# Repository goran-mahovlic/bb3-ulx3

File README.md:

# Mix of BB3 ULX3S

Current version does not have SDRAM on FPGA

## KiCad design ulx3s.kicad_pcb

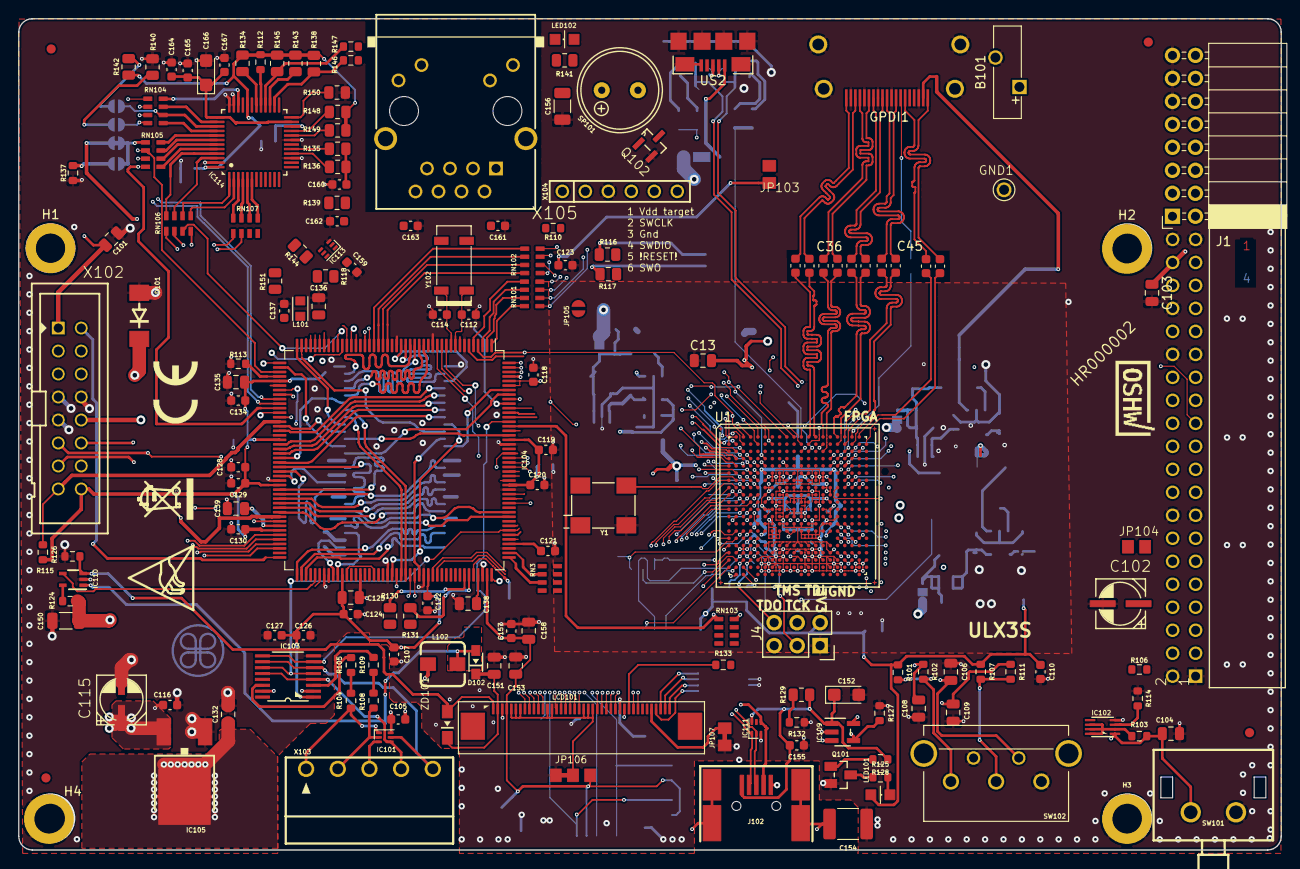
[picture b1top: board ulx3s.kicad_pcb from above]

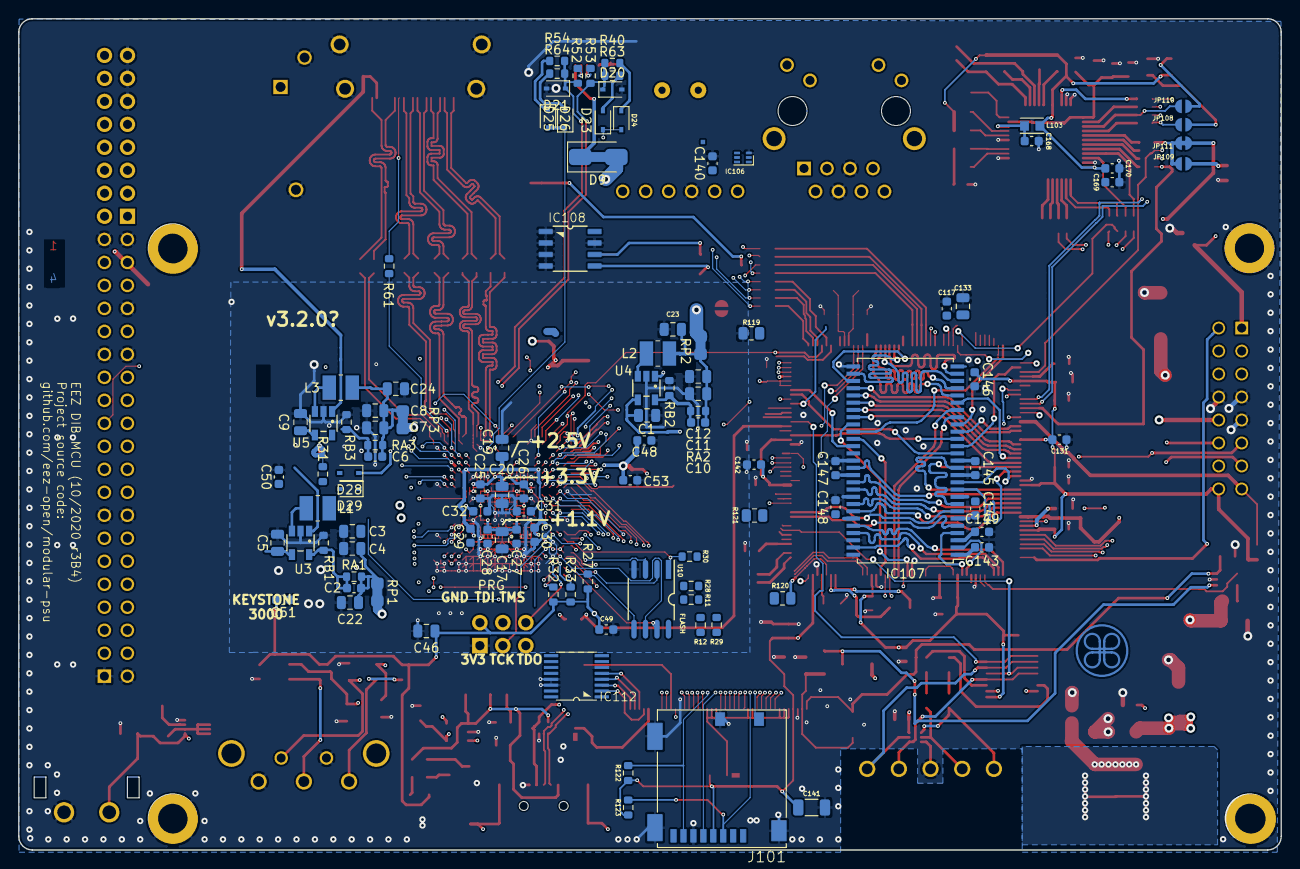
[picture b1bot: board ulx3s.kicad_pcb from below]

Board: 4 copper layers, 139.5 x 91.8 mm, 278 parts (104 on the bottom side), 327 nets.

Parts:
B101: DS1092-10-W6L; Battery_Panasonic_CR1025-VSK_Vertical_CircularHoles
C1, C3, C4, C5, C7, C8, C9, C11, C12: 22uF; C_0805_2012Metric
C2, C6, C10: 470pF; C_0603_1608Metric
C13, C17, C19, C20, C22, C23, C24, C46: 2.2uF; C_0805_2012Metric
C25, C26, C27, C28, C29, C30, C31, C32, C48, C49, C50, C51, C53: 22nF; C_0603_1608Metric
C36, C37, C38, C39, C40, C41, C42, C43, C44, C45: 220nF; C_0603_1608Metric
C101: N.C.; C_0805_2012Metric
C102, C115: EEEFK1V220R; PANASONIC_C
C103, C132, C133, C138, C139, C153: 2u2; C_0805_2012Metric
C104, C106, C108, C109: 10n; C_0805_2012Metric
C105, C107, C110, C116, C117, C118, C119, C120, C121, C122, C123, C124, C126, C127, C128, C129, C130, C131, C134, C137, C142, C143, C144, C145, C146, C147, C148, C149, C155, C157, C160, C161, C162, C163, C164, C165, C167, C168, C169, C170: 100n; C_0603_1608Metric
C112, C114: 4p7; C_0603_1608Metric
C125, C135, C136, C151, C158: 1u; C_0805_2012Metric
C140, C159: N.C.; C_0603_1608Metric
C141, C150, C156: 4u7; C_1206_3216Metric
C152: 4u7; CP_EIA-3216-10_Kemet-I
C154: 4n7/1kV; C_1812_4532Metric
C166: 10uF; CP_EIA-3216-10_Kemet-I
D9: 0; D_SMA_Jumper_NC
D20, D21: 3.6V; D_SOD-323
D23, D24, D25, D26, D28, D29: 1N914; D_SOD-323
D101: SMBJ5.0A-TR; DO214AA
D102: RB751V40T1G; SOD323-R
EEZ_SIGNATURE: SIGNATURESMALL; SIGNATURE_5MM
FM1, FM2, FM3, FM4: FIDUCIAL
GND1: PCB_TEST_TABSHIELD; PCB_SHIELD_TAB
GPDI1: GPDI-D; CONN-10029449-111RLF
H1, H2, H3, H4: HOLE; MountingHole_3.2mm_M3_ISO14580_Pad
IC101, IC111: TPD4E001DRLR; DRL6
IC102: 74AUP1G74DC.125; DCU8
IC103: CD74HC4050PWR; PW16
IC104: STM32F769IIT6; LQFP-176_24x24mm_P0.5mm
IC105: LD1117ADT33TR; DPACK
IC106, IC113: N.C.; DRL6
IC107: IS42S16400J; TSOP-II-54_22.2x10.16mm_P0.8mm
IC108: AT24C256C-SSHL-B; SOIC127P600X173-8N
IC109: TPS2051BDBVR; DBV5
IC110: TPS61169DCKR; DCK5
IC112: TSC2007IPW; PW(R-PDSO-G16)
IC114: DP83848CVV_NOPB; PT48
J1: Conn_02x08_Odd_Even; PinSocket_2x08_P2.54mm_Horizontal
J4: CONN_02X03; Socket_Strip_Straight_2x03
J101: 503398-1892; 5033981892
J102: 67803-8020; 678038020
JP103, JP104: JP2-CUT-0805; R_0805
JP105, JP108, JP109, JP110: JP2-CUT
JP106: JP3-CUT-0805-ROTATED; JP3-0805-CUT2
JP107: JP2-NOCUT-0805; JP2-0805-NOCUT
JP111: JP2-NOCUT
L1, L2, L3: 2.2uH; L_1008_1210
L101, L103: BLM18AG102SH1D; BEAD0603
L102: DLG-0403-4R7; DE0403
LABEL1: HR000002; CERT-SMALL-SILK
LCD101: 505110-4091; FPC_40
LED101, LED102: N.C.; LED_0805
Q101: N.C.; SOT23-BEC
Q102: 2N7002; SOT103P240X110-3N
R11, R12, R27, R28: 10k; R_0603_1608Metric
R29, R40, R54: 1.1k; R_0603_1608Metric
R30: 4.7k; R_0603_1608Metric
R31, R32, R33, R63, R64: 15k; R_0603_1608Metric
R52, R53: 27; R_0603_1608Metric
R61: 549; R_0603_1608Metric
R101, R104, R105, R107, R108, R109, R112, R115: 4K7; R_0603_1608Metric
R102, R103, R111, R113, R127, R132, R133: 10K; R_0603_1608Metric
R106, R110: 1K; R_0603_1608Metric
R114, R125, R128, R137: N.C.; R_0603_1608Metric
R116, R117, R134: 1K5; R_0805_2012Metric
R118: 47R; R_0805_2012Metric
R119, R120, R121, R140, R141, R142: N.C.; R_0805_2012Metric
R122, R123: 47K; R_0603_1608Metric
R124, R126: 10R; R_0603_1608Metric
R129: 4K7; R_0805_2012Metric
R130, R131: 22R; R_0805_2012Metric
R135, R136, R139, R144: 49R9; R_0805_2012Metric
R138, R143, R145, R148, R149, R151: 2K2; R_0805_2012Metric
R146, R147: 220R; R_0603_1608Metric
R150: 4K87; R_0805_2012Metric
RA1, RA2, RA3: 15k; R_0603_1608Metric
RB1: 18k; R_0603_1608Metric
RB2: 4.7k; R_0603_1608Metric
RB3: 3.3k; R_0603_1608Metric
RN3, RN101, RN102, RN103, RN104, RN105, RN106, RN107: DR1206-33R-4/8; CAY16
RP1, RP2, RP3: 0; R_0805_2012Metric_Pad1.29x1.40mm_HandSolder_Jumper_NC
SH101: SHORTNOHOLE; SHORT_NOHOLE
SP101: LD-BZEN 0903; LD-BZEN-0903
SW101: TL1100CF160Q; TL1100C
SW102: PEC16-2215F-S0024; PEC16-2215F
U1: LFE5U-85F-6BG381C; BGA-381_pitch0.8mm_dia0.4mm
U3, U4, U5: TLV62569DBV; TSOT-25
U10: IS25LP128F-JBLE; SOA008-150-208mil
U$1: RECYCLE_BIN1_8
U$2: CE_5MM
U$6: ESD_SYMBOL
US2: MICRO_USB; USB-MICRO-B-FCI-10118192-0001LF
X101: DS1024-2*20R0; ZL263-40DG
X102: DS1013-16SSIB1; IDC-16PIN
X103: 691322110005; MC1,5_5-G-3,5
X104: N.C.; SSW-106-02-S-S
X105: LMJTAB881243M-L; RJ45-TRAFO-LED
Y1: FNETHE025; Crystal_SMD_7050_4Pads
Y102: XTAL016178-85SMX; 85SMX
ZD101: BZX384-B24.115; SOD323-W

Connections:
+1V1: C17.1, C27.1, C28.1, J1.12, RP1.2, U1.H8, U1.H9, U1.H10, U1.H11, U1.H12, U1.H13, U1.J8, U1.J13, U1.K8, U1.K13, U1.L8, U1.L13, U1.M8, U1.M13, U1.N8, U1.N9, U1.N10, U1.N11, U1.N12, U1.N13, U1.T6, U1.T7, U1.T8, U1.T9, U1.T10, U1.T11, U1.T12, U1.T13, U1.T14, U1.T15, U1.U6, U1.U15
+2V5: C19.1, C29.1, C30.1, J1.14, RP2.2, U1.F6, U1.F15, U1.P6, U1.P15, U1.V10, U1.V11, U1.V17, U1.V18
+3V3: C13.2, C20.1, C25.1, C26.1, C31.1, C32.1, C46.1, C48.1, C49.1, C50.1, C51.1, C53.1, C102.1, C107.1, C110.1, C117.1, C118.1, C119.1, C120.1, C121.1, C122.1, C124.1, C125.1, C126.1, C127.1, C128.1, C129.1, C130.1, C131.1, C132.1, C133.1, C134.1, C135.1, C140.1, C141.1, C142.2, C143.1, C144.1, C145.1, C146.1, C147.1, C148.1, C149.1, C153.1, C156.2, C157.2, C158.2, C159.1, C169.1, C170.1, IC102.2, IC102.6, IC102.7, IC102.8, IC103.1, IC104.15, IC104.23, IC104.36, IC104.49, IC104.62, IC104.72, IC104.82, IC104.96, IC104.99, IC104.118, IC104.131, IC104.136, IC104.149, IC104.159, IC104.171, IC104.172, IC105.4, IC106.6, IC107.1, IC107.3, IC107.9, IC107.14, IC107.27, IC107.43, IC107.49, IC108.8, IC112.1, IC113.6, IC114.32, IC114.48, J1.16, J4.2, J101.4, JP105.1, JP106.NO, L101.P$1, L103.P$1, LCD101.4, LED101.A, R11.1, R12.1, R27.1, R28.1, R29.1, R30.1, R31.1, R32.1, R33.1, R101.1, R103.1, R107.1, R112.1, R115.1, R116.1, R117.1, R122.1, R123.1, R133.2, R134.2, R138.1, R141.1, R142.1, R143.1, R145.1, R148.1, R149.1, R151.1, RP3.2, SH101.P$2, U1.F9, U1.F10, U1.F11, U1.F12, U1.H6, U1.H7, U1.H14, U1.H15, U1.J6, U1.J15, U1.L6, U1.L7, U1.L14, U1.L15, U1.M6, U1.M15, U1.P9, U1.P10, U1.T2, U1.T3, U1.T4, U1.U2, U10.8, X101.7, X102.16, X105.9, X105.12, Y1.1, Y1.4
+3V3(A): C161.2, C163.2, C168.1, IC114.22, L103.P$2, X105.3, X105.6
+5V: C1.1, C5.1, C9.1, C105.1, C115.1, C116.1, C150.1, D9.2, D101.C, GPDI1.18, IC101.6, IC105.3, IC109.5, L102.1, R124.1, U3.1, U3.4, U4.1, U4.4, U5.1, U5.4, X101.35, X101.36, X102.5, X102.6
+12V: C103.1, X101.37, X101.38, X102.3, X102.4
+VAUX: JP103.2, X102.10
+VAUX_OUT: JP104.2, X101.5
/Envox SDRAM/TCK: IC106.1, R121.2, X104.2
/Envox SDRAM/TMS: IC106.2, R120.2, X104.4
/Envox_STM32/BYPASS_REG: IC104.48, R113.2
/Envox_STM32/RCC_OSC32_IN: C112.1, IC104.9, Y102.1
/Envox_STM32/RCC_OSC32_OUT: C114.1, IC104.10, Y102.4
/Envox_STM32/VBAT: B101.+, C123.1, IC104.6, JP103.1, JP104.1
/Envox_STM32/VCAP1: C139.1, IC104.81
/Envox_STM32/VCAP2: C138.1, IC104.129
/Envox_STM32/VDDA: C136.1, C137.1, IC104.39, L101.P$2, R118.2
/Envox_STM32/VREF+: IC104.38, R118.1
/Ethernet/LED_ACT: IC114.26, R138.2, R146.2
/Ethernet/LED_LINK: IC114.28, R145.2, R147.2
/Ethernet/LED_SPEED: IC114.27, LED102.C, R143.2
/TFT_LCD/LCD_DISP: LCD101.31, R133.1
/TFT_LCD/USB_D_N: IC111.1, J102.2, R130.1
/TFT_LCD/USB_D_P: IC111.2, J102.3, R131.1
/TFT_LCD/VLED+: C151.1, D102.C, LCD101.2, ZD101.C
/TFT_LCD/VLED-: IC110.3, LCD101.1, R126.1, ZD101.A
/TFT_LCD/XL: IC112.4, LCD101.39
/TFT_LCD/XR: IC112.2, LCD101.37
/TFT_LCD/YD: IC112.5, LCD101.38
/TFT_LCD/YU: IC112.3, LCD101.40
/flash/FLASH_MISO: R28.2, U1.V2, U10.2
/flash/FLASH_MOSI: R27.2, U1.W2, U10.5
/flash/FLASH_SCK: R29.2, U1.U3, U10.6
/flash/FLASH_nCS: R30.2, U1.R2, U10.1
/flash/FLASH_nHOLD: R12.2, U1.W1, U10.7
/flash/FLASH_nWP: R11.2, U1.Y2, U10.3
/flash/FPGA_DONE: R32.2, U1.Y3
/flash/FPGA_INITN: R33.2, U1.V3
/flash/FPGA_PROGRAMN: D28.2, D29.2, R31.2, U1.W3
/gpdi/FPDI_CEC: R61.2, U1.A18
/gpdi/GPDI_CLK+: C45.2, GPDI1.10
/gpdi/GPDI_CLK-: C41.2, GPDI1.12
/gpdi/GPDI_D0+: C44.2, GPDI1.7
/gpdi/GPDI_D0-: C40.2, GPDI1.9
/gpdi/GPDI_D1+: C43.2, GPDI1.4
/gpdi/GPDI_D1-: C39.2, GPDI1.6
/gpdi/GPDI_D2+: C42.2, GPDI1.1
/gpdi/GPDI_D2-: C38.2, GPDI1.3
/gpdi/GPDI_ETH+: C36.2, GPDI1.14
/gpdi/GPDI_ETH-: C37.2, GPDI1.19
/power/FB1: C2.2, RA1.2, RB1.2, U3.5
/power/FB2: C10.2, RA2.2, RB2.2, U4.5
/power/FB3: C6.2, RA3.2, RB3.2, U5.5
/power/L1: L1.1, U3.3
/power/L2: L2.1, U4.3
/power/L3: L3.1, U5.3
/power/P1V1: C2.1, C3.1, C4.1, C22.1, L1.2, RA1.1, RP1.1
/power/P2V5: C10.1, C11.1, C12.1, C23.1, L2.2, RA2.1, RP2.1
/power/P3V3: C6.1, C7.1, C8.1, C24.1, L3.2, RA3.1, RP3.1
/usb/FPD+: R53.2, US2.3
/usb/FPD-: R52.2, US2.2
/usb/US2VBUS: D9.1, US2.1
BOOT0: IC102.3, IC104.166, R114.2
CLK_25MHz: U1.G2, Y1.3
CLK_TO_ETH: RN104.1, U1.B11
CLK_TO_STM32: IC104.29, U1.A9
DAC_OUT1: IC104.50, Q102.1
DIN2: IC104.8, R110.2
DOUT2: IC103.7, IC103.9, IC104.163
ENC_A: C108.2, IC104.119, R102.1
ENC_B: C109.1, IC104.120, R111.1
ENC_SW: C106.2, IC104.173, SW102.E
ETH_COL: IC104.47, RN105.2
ETH_CRS: IC104.40, JP108.1, RN104.4
ETH_MDC: IC104.33, IC114.31
ETH_MDIO: IC104.42, IC114.30, R134.1
ETH_RXD0: IC104.54, RN105.3
ETH_RXD1: IC104.55, RN105.4
ETH_RXD2: IC104.83, RN106.1
ETH_RXD3: IC104.84, RN106.2
ETH_RX_CLK: IC104.41, RN104.2
ETH_RX_DV: IC104.53, RN104.3
ETH_RX_ERR: IC104.79, JP111.2
ETH_TXD0: IC104.85, RN107.1
ETH_TXD1: IC104.86, RN107.2
ETH_TXD2: IC104.34, RN107.3
ETH_TXD3: IC104.167, RN107.4
ETH_TX_CLK: IC104.35, RN106.3
ETH_TX_EN: IC104.80, RN106.4
FMC_A0: IC104.16, IC107.23
FMC_A1: IC104.17, IC107.24
FMC_A2: IC104.18, IC107.25
FMC_A3: IC104.19, IC107.26
FMC_A4: IC104.20, IC107.29
FMC_A5: IC104.21, IC107.30
FMC_A6: IC104.60, IC107.31
FMC_A7: IC104.63, IC107.32
FMC_A8: IC104.64, IC107.33
FMC_A9: IC104.65, IC107.34
FMC_A10: IC104.66, IC107.22
FMC_A11: IC104.67, IC107.35
FMC_A12: IC104.110, IC107.36
FMC_BA0: IC104.112, IC107.20
FMC_BA1: IC104.113, IC107.21
FMC_D0: IC104.97, IC107.2
FMC_D1: IC104.98, IC107.4
FMC_D2: IC104.142, IC107.5
FMC_D3: IC104.143, IC107.7
FMC_D4: IC104.68, IC107.8
FMC_D5: IC104.69, IC107.10
FMC_D6: IC104.70, IC107.11
FMC_D7: IC104.73, IC107.13
FMC_D8: IC104.74, IC107.42
FMC_D9: IC104.75, IC107.44
FMC_D10: IC104.76, IC107.45
FMC_D11: IC104.77, IC107.47
FMC_D12: IC104.78, IC107.48
FMC_D13: IC104.89, IC107.50
FMC_D14: IC104.90, IC107.51
FMC_D15: IC104.91, IC107.53
FMC_NBL0: IC104.169, IC107.15
FMC_NBL1: IC104.170, IC107.39
FMC_SDCKE0: IC104.43, IC107.37
FMC_SDCLK: IC104.116, IC107.38
FMC_SDNCAS: IC104.160, IC107.17
FMC_SDNE0: IC104.44, IC107.19
FMC_SDNRAS: IC104.59, IC107.18
FMC_SDNWE: IC104.46, IC107.16
FPDI_CLK+: C45.1, U1.A17
FPDI_CLK-: C41.1, U1.B18
FPDI_D0+: C44.1, U1.A16
FPDI_D0-: C40.1, U1.B16
FPDI_D1+: C43.1, U1.A14
FPDI_D1-: C39.1, U1.C14
FPDI_D2+: C42.1, U1.A12
FPDI_D2-: C38.1, U1.A13
FPDI_ETH+: C36.1, U1.A19
FPDI_ETH-: C37.1, U1.B20
GND: B101.-, C1.2, C3.2, C4.2, C5.2, C7.2, C8.2, C9.2, C11.2, C12.2, C13.1, C17.2, C19.2, C20.2, C22.2, C23.2, C24.2, C25.2, C26.2, C27.2, C28.2, C29.2, C30.2, C31.2, C32.2, C46.2, C48.2, C49.2, C50.2, C51.2, C53.2, C101.1, C102.2, C103.2, C104.1, C105.2, C106.1, C107.2, C108.1, C109.2, C110.2, C112.2, C114.2, C115.2, C116.2, C117.2, C118.2, C119.2, C120.2, C121.2, C122.2, C123.2, C124.2, C125.2, C126.2, C127.2, C128.2, C129.2, C130.2, C131.2, C132.2, C133.2, C134.2, C135.2, C136.2, C137.2, C138.2, C139.2, C140.2, C141.2, C142.1, C143.2, C144.2, C145.2, C146.2, C147.2, C148.2, C149.2, C150.2, C151.2, C152.2, C153.2, C154.1, C155.1, C156.1, C157.1, C158.1, C159.2, C160.2, C161.1, C162.2, C163.1, C164.2, C165.2, C166.2, C167.2, C168.2, C169.2, C170.2, D20.2, D21.2, D101.A, GND1.1, GPDI1.0, GPDI1.2, GPDI1.5, GPDI1.8, GPDI1.11, GPDI1.17, H1.1, H2.1, H3.1, H4.1, IC101.3, IC102.4, IC103.8, IC104.7, IC104.14, IC104.22, IC104.37, IC104.61, IC104.71, IC104.95, IC104.103, IC104.109, IC104.117, IC104.130, IC104.135, IC104.148, IC104.158, IC105.1, IC106.3, IC107.6, IC107.12, IC107.28, IC107.41, IC107.46, IC107.52, IC107.54, IC108.1, IC108.2, IC108.3, IC108.4, IC108.7, IC109.2, IC110.2, IC111.3, IC112.6, IC112.13, IC112.14, IC113.3, IC114.15, IC114.19, IC114.35, IC114.36, IC114.47, J1.11, J1.13, J1.15, J4.1, J101.6, J101.S, J101.S1, J101.S2, J101.SW2, J102.5, JP106.NC, JP107.2, LCD101.3, LCD101.29, Q101.E, Q102.2, R113.1, R114.1, R119.1, R126.2, R127.1, R132.2, R137.1, R140.1, R150.1, RB1.1, RB2.1, RB3.1, SW101.2, SW102.C, SW102.D, U1.B7, U1.B14, U1.C19, U1.D4, U1.F7, U1.F8, U1.F13, U1.F14, U1.G4, U1.G6, U1.G7, U1.G8, U1.G9, U1.G10, U1.G11, U1.G12, U1.G13, U1.G14, U1.G15, U1.G17, U1.H19, U1.J2, U1.J7, U1.J9, U1.J10, U1.J11, U1.J12, U1.J14, U1.K6, U1.K7, U1.K9, U1.K10, U1.K11, U1.K12, U1.K14, U1.K15, U1.L9, U1.L10, U1.L11, U1.L12, U1.M2, U1.M7, U1.M9, U1.M10, U1.M11, U1.M12, U1.M14, U1.M16, U1.N6, U1.N7, U1.N14, U1.N15, U1.P7, U1.P8, U1.P11, U1.P12, U1.P13, U1.P14, U1.R4, U1.R19, U1.U4, U1.U7, U1.U8, U1.U9, U1.U10, U1.U11, U1.U12, U1.U13, U1.U14, U1.V5, U1.V6, U1.V7, U1.V8, U1.V9, U1.V12, U1.V13, U1.V14, U1.V15, U1.V16, U1.V19, U1.V20, U1.W6, U1.W7, U1.W12, U1.W15, U1.W16, U1.W19, U3.2, U4.2, U5.2, U10.4, US2.5, US2.6, X101.1, X101.2, X101.15, X101.16, X101.29, X101.30, X101.34, X101.39, X101.40, X102.7, X102.8, X102.9, X103.3, X104.3, X105.4, X105.5, Y1.2
GPDI_CEC: GPDI1.13, R61.1
I2C1_SCL: IC104.164, IC108.6, IC112.12, R116.2, U1.U18, X101.12, X102.13
I2C1_SDA: IC104.165, IC108.5, IC112.11, R117.2, U1.U16, X101.14, X102.14
IRQ_TOUCH: IC104.151, IC112.10
JTAG_TCK: J4.4, U1.T5
JTAG_TDI: J4.3, U1.R5
JTAG_TDO: J4.6, U1.V4
JTAG_TMS: J4.5, U1.U5
LTDC_FROM_FPGA_B3: LCD101.24, U1.P2
LTDC_FROM_FPGA_B4: LCD101.25, U1.P3
LTDC_FROM_FPGA_B5: LCD101.26, U1.R1
LTDC_FROM_FPGA_B6: LCD101.27, U1.P4
LTDC_FROM_FPGA_B7: LCD101.28, U1.T1
LTDC_FROM_FPGA_CLK: LCD101.30, U1.L4
LTDC_FROM_FPGA_DE: LCD101.34, U1.U17
LTDC_FROM_FPGA_G2: LCD101.15, U1.J1
LTDC_FROM_FPGA_G3: LCD101.16, U1.J3
LTDC_FROM_FPGA_G4: LCD101.17, U1.K4
LTDC_FROM_FPGA_G5: LCD101.18, U1.K3
LTDC_FROM_FPGA_G6: LCD101.19, U1.L1
LTDC_FROM_FPGA_G7: LCD101.20, U1.J4
LTDC_FROM_FPGA_HSYNC: LCD101.32, U1.U1
LTDC_FROM_FPGA_R3: LCD101.8, U1.E6
LTDC_FROM_FPGA_R4: LCD101.9, U1.E9
LTDC_FROM_FPGA_R5: LCD101.10, U1.J5
LTDC_FROM_FPGA_R6: LCD101.11, U1.G1
LTDC_FROM_FPGA_R7: LCD101.12, U1.H2
LTDC_FROM_FPGA_VSYNC: LCD101.33, U1.V1
LTDC_TO_FPGA_B3: IC104.154, U1.E1
LTDC_TO_FPGA_B4: IC104.155, U1.F4
LTDC_TO_FPGA_B5: IC104.174, U1.B3
LTDC_TO_FPGA_B6: IC104.175, U1.F5
LTDC_TO_FPGA_B7: IC104.176, U1.E5
LTDC_TO_FPGA_CLK: IC104.115, U1.G5
LTDC_TO_FPGA_DE: IC104.28, U1.D3
LTDC_TO_FPGA_G2: IC104.52, U1.B2
LTDC_TO_FPGA_G3: IC104.153, U1.F1
LTDC_TO_FPGA_G4: IC104.45, U1.D2
LTDC_TO_FPGA_G5: IC104.132, U1.H3
LTDC_TO_FPGA_G6: IC104.13, U1.E2
LTDC_TO_FPGA_G7: IC104.145, U1.G3
LTDC_TO_FPGA_HSYNC: IC104.12, U1.D1
LTDC_TO_FPGA_R3: IC104.56, U1.E3
LTDC_TO_FPGA_R4: IC104.51, U1.E4
LTDC_TO_FPGA_R5: IC104.32, U1.C3
LTDC_TO_FPGA_R6: IC104.57, U1.C2
LTDC_TO_FPGA_R7: IC104.114, U1.H4
LTDC_TO_FPGA_VSYNC: IC104.11, U1.C1
unnamed: C152.1, C155.2, IC109.1, IC111.6, J102.1, R128.1, R129.1
unnamed: C160.1, R135.1, R136.2
unnamed: C162.1, R139.1, R144.2
unnamed: C164.1, C165.1, C166.1, C167.1, IC114.18, IC114.23, IC114.37
unnamed: D23.2, R63.1
unnamed: D24.1, R40.1
unnamed: D25.2, R64.1
unnamed: D26.1, R54.2
unnamed: D102.A, IC110.1, L102.2
unnamed: IC101.1, R104.1, X103.1
unnamed: IC101.2, R108.1, X103.2
unnamed: IC101.4, IC103.4, IC103.12, X103.4
unnamed: IC101.5, IC103.6, IC103.10, X103.5
unnamed: IC103.2, R110.1
unnamed: IC103.3, R109.2
unnamed: IC103.14, R105.2
unnamed: IC103.15, R106.1
unnamed: IC104.1, RN101.8
unnamed: IC104.2, RN101.7
unnamed: IC104.3, RN101.6
unnamed: IC104.5, RN101.5
unnamed: IC104.24, RN102.8
unnamed: IC104.25, RN102.7
unnamed: IC104.26, RN102.6
unnamed: IC104.27, RN102.5
unnamed: IC104.92, RN3.8
unnamed: IC104.100, IC104.106
unnamed: IC104.133, RN3.7
unnamed: IC104.134, RN3.6
unnamed: IC104.162, RN103.5
unnamed: IC110.5, R124.2
unnamed: IC113.1, IC114.17, R135.2, X105.1
unnamed: IC113.2, IC114.16, R136.1, X105.2
unnamed: IC113.4, IC114.14, R139.2, X105.7
unnamed: IC113.5, IC114.13, R144.1, X105.8
unnamed: IC114.1, RN106.6
unnamed: IC114.2, RN106.5
unnamed: IC114.3, RN107.8
unnamed: IC114.4, RN107.7
unnamed: IC114.5, RN107.6
unnamed: IC114.6, RN107.5
unnamed: IC114.7, R151.2
unnamed: IC114.20, R149.2
unnamed: IC114.21, R148.2
unnamed: IC114.24, R150.2
unnamed: IC114.34, RN104.8
unnamed: IC114.38, RN104.7
unnamed: IC114.39, JP110.2, RN104.6
unnamed: IC114.40, RN104.5
unnamed: IC114.41, RN105.8
unnamed: IC114.42, RN105.7
unnamed: IC114.43, RN105.6
unnamed: IC114.44, RN105.5
unnamed: IC114.45, RN106.8
unnamed: IC114.46, RN106.7
unnamed: JP105.2, R119.2, X104.1
unnamed: JP106.COM, LCD101.5, LCD101.6, LCD101.7, LCD101.13, LCD101.14, LCD101.21, LCD101.22, LCD101.23
unnamed: JP107.1, LCD101.36
unnamed: JP108.2, R140.2
unnamed: JP109.1, JP111.1, RN105.1
unnamed: JP109.2, R137.2
unnamed: JP110.1, R142.2
unnamed: LED101.C, R125.2
unnamed: LED102.A, R141.2
unnamed: Q101.B, R128.2
unnamed: Q101.C, R125.1
unnamed: Q102.3, SP101.-B
unnamed: R101.2, R102.2, SW102.A
unnamed: R104.2, R105.1
unnamed: R107.2, R111.2, SW102.B
unnamed: R108.2, R109.1
unnamed: R146.1, X105.11
unnamed: R147.1, X105.10
unnamed: SH101.P$1, SP101.+B
unnamed: SW102.GND1, SW102.GND2
OE_SYNC: IC104.94, X101.10
PE: C101.2, C154.2, J102.SH1, J102.SH1.1, J102.SH2, J102.SH2.2, X102.1, X105.SH, X105.SH2
PWR_DIRECT: IC104.150, X102.12
PWR_SSTART: IC104.111, X102.11
RTC_REF: IC104.88, X102.2
SDMMC1_FROM_FPGA_CK: J101.5, U1.L3
SDMMC1_FROM_FPGA_CMD: J101.3, R123.2, U1.H1
SDMMC1_FROM_FPGA_D0: J101.7, R122.2, U1.N5
SD_FROM_FPGA_DETECT: J101.SW1, U1.K5
SPI2_FROM_FPGA_CLK: U1.C11, X101.32
SPI2_FROM_FPGA_CSA: U1.D16, X101.28
SPI2_FROM_FPGA_CSB: U1.D17, X101.27
SPI2_FROM_FPGA_IRQ: U1.E17, X101.25
SPI2_FROM_FPGA_MISO: U1.P17, X101.31
SPI2_FROM_FPGA_MOSI: U1.M17, X101.33
SPI2_TO_FPGA_CLK: RN3.2, U1.L16
SPI2_TO_FPGA_CSA: RN103.4, U1.P16
SPI2_TO_FPGA_CSB: RN3.1, U1.R18
SPI2_TO_FPGA_IRQ: IC104.123, U1.N16
SPI2_TO_FPGA_MISO: IC104.87, U1.N17
SPI2_TO_FPGA_MOSI: RN3.3, U1.R17
SPI4_FROM_FPGA_CLK: U1.A11, X101.23
SPI4_FROM_FPGA_CSA: U1.H17, X101.22
SPI4_FROM_FPGA_CSB: U1.H16, X101.21
SPI4_FROM_FPGA_IRQ: U1.C18, X101.19
SPI4_FROM_FPGA_MISO: U1.C17, X101.24
SPI4_FROM_FPGA_MOSI: U1.B17, X101.26
SPI4_TO_FPGA_CLK: RN101.1, U1.A10
SPI4_TO_FPGA_CSA: RN101.3, U1.B1
SPI4_TO_FPGA_CSB: RN101.2, U1.A5
SPI4_TO_FPGA_IRQ: IC104.168, U1.A2
SPI4_TO_FPGA_MISO: IC104.4, U1.A3
SPI4_TO_FPGA_MOSI: RN101.4, U1.A4
SPI5_FROM_FPGA_CLK: U1.B10, X101.17
SPI5_FROM_FPGA_CSA: U1.F17, X101.11
SPI5_FROM_FPGA_CSB: U1.D18, X101.13
SPI5_FROM_FPGA_IRQ: U1.H18, X101.9
SPI5_FROM_FPGA_MISO: U1.G18, X101.18
SPI5_FROM_FPGA_MOSI: U1.L17, X101.20
SPI5_TO_FPGA_CLK: RN102.2, U1.H5
SPI5_TO_FPGA_CSA: RN102.1, U1.B5
SPI5_TO_FPGA_CSB: IC104.156, U1.F2
SPI5_TO_FPGA_IRQ: IC104.138, U1.R16
SPI5_TO_FPGA_MISO: RN102.3, U1.A6
SPI5_TO_FPGA_MOSI: RN102.4, U1.D6
SYS_JTCK-SWCLK: IC104.137, R121.1
SYS_JTDO-SWO: IC104.161, IC106.5, X104.6
SYS_JTMS-SWDIO: IC104.128, R120.1
TFT_BRIGHTNESS: IC104.93, IC110.4
UART_RX/DIN1: IC104.140, R106.2, X101.3
UART_TX/DOUT1: IC103.5, IC103.11, IC104.139, X101.4
USB_FPGA_D+: D20.1, R40.2, R53.1, R63.2, U1.D15, U1.E16
USB_FPGA_D-: D21.1, R52.1, R54.1, R64.2, U1.E15, U1.F16
USB_FPGA_PULL_D+: D23.1, D24.2, U1.B12
USB_FPGA_PULL_D-: D25.1, D26.2, U1.C12
USB_OTG_FS_D_N: IC104.126, R130.2
USB_OTG_FS_D_P: IC104.127, R131.2
USB_OTG_FS_ID: IC104.125, IC111.4, J102.4
USB_OTG_FS_PSO: IC104.147, IC109.4, R127.2
USB_OTG_FS_VBUS: IC104.124, R129.2, R132.1
USER_PROGRAMN: D29.1, U1.M4
USER_SW: C104.2, IC102.1, IC104.152, R103.2, SW101.1
~FAULT: IC104.58, R115.2, X101.8, X102.15
~RESET: IC104.31, IC106.4, IC114.29, R112.2, X101.6, X104.5
~USB_OTG_FS_OC: IC104.146, IC109.3

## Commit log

2020-10-15 First pass cleanup
2020-10-15 More cleanup - moving flash and crystal
2020-10-15 Moving power closer
2020-10-15 Adding schematics
2020-10-15 Assigning parts - netlitst to pcb
2020-10-16 Frame around FPGA
2020-10-16 Moving around
2020-10-16 New annotation - All STM32 parts are +100
2020-10-16 All STM32 parts are now +100, moving parts to original position
2020-10-16 Adding dimensions
2020-10-16 Combined
2020-10-16 Adding default parts
2020-10-16 Board update
2020-10-16 Adding 3D models
2020-10-16 Update 3D models, start to send pins to FPGA
2020-10-17 Adding TO FROM FPGA lines
2020-10-17 Rewiering LCD OUT to bottom left
2020-10-18 Removing BUS from STM32 - cleanup direct connections
2020-10-18 LCD connector cleanup
2020-10-18 SDRAM cleanup
2020-10-18 PCB update
2020-10-18 More schematics cleanup
2020-10-18 Adding new PCB with new wire imports
2020-10-18 better RGB-OUT
2020-10-18 More fixes
2020-10-19 Adding all SPI to FPGA resorting LCD TO FPGA
2020-10-19 Adding woutrd SDRAM
2020-10-19 SDRAM footprint change
2020-10-19 STM32 footprint change
2020-10-19 Partial copied SDRAM routing from BB3
2020-10-19 Locking logos
2020-10-20 Before autorouter
2020-10-20 Adding SPI from FPGA
2020-10-20 Smaller Text
2020-10-20 Almost ready for routing
2020-10-21 Moving clock
2020-10-21 Before delete
2020-10-21 Cleaning errors
2020-10-21 Routing FPGA to LCD
2020-10-21 GPDI routed
2020-10-21 Routing right side
2020-10-22 Adding DIB_V2 connector for SERDES, change battery, initial power fixes power
2020-10-22 Routing power
2020-10-22 before autoroute check
2020-10-22 Fixing 2V5_3V3 error, fixing BTN line left
2020-10-22 Routing long signals
2020-10-22 Clearup middle - more routing
2020-10-22 Almost there
2020-10-22 Finish routing - removing CE and OpenHW number
2020-10-23 Routing SERDES
2020-10-23 Finished initial routing
2020-10-26 V0.1
2020-10-26 Production V_0.1
2020-10-26 Silk screen update
2020-10-26 Silkscreen
2020-10-26 New gerbers
2020-10-26 Moving ETH parts - silkscreen
2020-10-26 Aditional groundung
2020-10-27 Grounding fixes, production V_01
